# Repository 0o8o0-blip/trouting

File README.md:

# Trouting: an autorouter for KiCad

Trouting (short for *Tommy's routing*) routes the tracks of a KiCad PCB for you. Give it a placed board with
a GND pour; it routes every net, stitches GND into the pour with vias, writes
the tracks back into the `.kicad_pcb` and runs KiCad's own DRC on the result.

*The demo board in `examples/demo/`, routed by Trouting in 24 seconds: 25
nets, every pad connected, no new DRC violations. Red is the front, blue is the GND
pour on the back with the back-side tracks cut into it.*

It is made for the boards most of us actually make: dense **2-layer boards with
a ground pour**, QFNs, an ESP32 module, fine-pitch connectors.

- **All nets at once.** It doesn't route one net after another and get stuck
  on the last few. Every net is routed every round, and spots that several
  nets want get more expensive each round (negotiated congestion, the
  PathFinder algorithm from FPGA routing). The net that has another way moves;
  the one that needs the spot keeps it.
- **Understands pours.** GND isn't routed pad to pad: each pad gets a short
  track and a via into the pour. Trouting predicts how KiCad will fill the
  zones, so it knows which bits of pour will be cut off, and stitches those
  too. Thermal reliefs are checked the way KiCad's DRC checks them.
- **Your board's rules.** Clearances, track widths and via sizes come from
  the board's net classes (`.kicad_pro`) and custom rules (`.kicad_dru`).
  Power nets keep their width where it fits and narrow only where it doesn't,
  and you are told where.
- **Checked by KiCad.** After routing, KiCad's DRC runs on the result and
  Trouting reports any violation that wasn't there before.
- **Native to KiCad.** No Java and no Specctra DSN/SES export and import. It
  reads and writes the `.kicad_pcb` through KiCad's own Python module.

Status: young but working. On the public [PCBWorld](https://github.com/LGAI-Research/PCBWorld)
benchmark it routes all 119 boards fully connected and free of DRC errors (see Results). It runs
on Linux, Windows and macOS with KiCad 9 and 10.

## In KiCad: the plugin

Trouting can run from KiCad's PCB editor: a toolbar button routes the open
board, and Ctrl+Z takes the routes out again. When the board can't be routed
as placed, the result window lists the suggested moves, and "Make this move
and route again" does just that.

To install it, download the `trouting-…-pcm.zip` from the
[latest release](https://github.com/TommyHolt/trouting/releases/latest). In
KiCad, open **Plugin and Content Manager > Install from File**, pick the zip,
then restart the PCB editor. The same zip works on Linux, Windows and macOS.

From a checkout, `python3 tools/make_pcm.py` builds the zip into `dist/`, and
on Linux `tools/install_plugin.sh` links the plugin into KiCad instead, for
development.

The first time you click it, it asks to install numpy, scipy and shapely into
its own folder: a 55 MB download, with KiCad's pip (KiCad's AppImage has none:
then the plugin fetches the same packages from PyPI itself, each checked
against PyPI's SHA-256). The router runs in a
process of its own, so the editor stays responsive and you can cancel.

It works with KiCad 9 and 10 on Linux, 64-bit Windows and macOS (Apple
Silicon and Intel). On Linux it is tested with the KiCad 9 snap and KiCad's
AppImage. On Windows, on an Apple Silicon Mac and with the AppImage on Linux,
every change is tested on GitHub Actions with KiCad 9 and 10 from their
installers: the package install and the whole routing run, up to a clean DRC.
The Intel Mac build is made but not tested.

It routes 12 setups at once and keeps the best, so it is quicker the more cores
you have: the stuck demo below, suggestions included, takes about 7 minutes on
12 cores and over 20 on 4. It runs no more setups at once than fit in the free
memory (each needs a few hundred MB on a typical board), so it won't push the
machine into swap. It takes as long as it needs; `--max-minutes M`
stops it after M minutes, when each setup keeps its best try and the nets it
couldn't route are listed.

## From the command line

You need:

- **KiCad 9 or 10.** On Linux, tested with the snap (`sudo snap install kicad`); a
  normal install should also work if your system Python can `import pcbnew`.
  On Windows, the normal installer: Trouting finds KiCad in Program Files (or
  set `KICAD_PYTHON` to the `python.exe` in KiCad's `bin` folder). On macOS,
  KiCad in Applications: Trouting finds the Python inside `KiCad.app` (or set
  `KICAD_PYTHON`).
- **Python 3.9 or newer** with numpy, scipy, shapely and Pillow.
- **A C compiler**, for the search core, a small C file compiled the first time
  it runs. On Linux, gcc. On macOS, clang (`xcode-select --install`). On
  Windows, either gcc from MinGW-w64, or no compiler: copy
  `plugins/trouting/prebuilt/core-…-win32-amd64.dll` out of the release zip
  into `trouting/prebuilt/`.

```sh
git clone https://github.com/TommyHolt/trouting.git
cd trouting
pip install -r requirements.txt
```

Then:

```sh
./trouting.py board.kicad_pcb                      # route in place, keeps board.kicad_pcb.trouting-bak
./trouting.py board.kicad_pcb -o routed.kicad_pcb  # write somewhere else
./trouting.py board.kicad_pcb --keep-tracks        # keep the tracks already there, route the rest
./trouting.py board.kicad_pcb --png routed.png     # also draw the result: front red, back blue, vias white
./trouting.py board.kicad_pcb --plane-cost 1000    # keep signal tracks off the plane layers where it can
```

On Windows, run it as `python trouting.py …`. On macOS, `python3 trouting.py …`
keeps the Mac awake while it routes (it uses `caffeinate`).

To try it on the demo board (a made-up USB-C microcontroller board, placed
but not routed):

```sh
./trouting.py examples/demo/demo.kicad_pcb -o demo-routed.kicad_pcb
./trouting.py examples/demo/stuck.kicad_pcb -o stuck-routed.kicad_pcb   # placed too tight: shows the suggestions
```

Close the board in KiCad first, or reload it after. Keep the `.kicad_pro` (and
`.kicad_dru`, if you have one) next to the `.kicad_pcb`: that is where the net
classes and rules are. Tracks you have **locked** in KiCad are kept.

It runs twelve router setups in parallel (one per core) and keeps the best: the
fewest unrouted connections, then the fewest vias, then the shortest copper.
A run looks like this:

```
reading board.kicad_pcb
  dumped 2 copper layers, 50 footprints, 70 pads, 13 nets, 0 tracks, 0 vias
board read: 1003 x 503 cells x 2 layers, 13 nets to join (0.8s)
  setup via  8.0, plane 1.0:  0 unrouted,   0 vias,    184 mm  (1 rounds, 0s)
  setup via  8.0, plane 1.5:  0 unrouted,  14 vias,    186 mm  (4 rounds, 1s)
  ...
best: via cost 8.0, plane cost 1.0
  applied 66 tracks, 0 vias
wrote board.kicad_pcb  (5s)

all connections routed
KiCad DRC: 0 unconnected pads (was 0)
  no new violations
```

### When a board can't be routed as placed

Then Trouting looks for a part to move or rotate. It takes the parts near the
connections it couldn't make and tries turning them and shifting them by 0.5
to 2 mm. A move must keep the part's courtyard clear of the other parts, its
pads clear of other copper, and the part as far inside the board as it was.
Trouting ranks the moves by how much shorter and less tangled the ratsnest
gets, then routes the whole board with each of the best ones. Only moves that
leave fewer connections unrouted are listed. On `examples/demo/stuck.kicad_pcb`
(the demo with U1 turned and C5 moved up):

```
not routed (3):
  ADC1                     U1.10
  SDA                      U1.13
  TX                       U1.11
  crowded at: (123.50, 112.30)
to make it route, move or rotate a part (each checked by routing the board with it):
  move C5 0.5 mm right and down (to 124.15, 114.15)  routes fully
  move C5 2.0 mm down (to 123.80, 115.80)            routes fully
  rotate U1 90° clockwise (to 0°)                    2 left unrouted
  move U1 1.0 mm down (to 120.00, 114.00)            2 left unrouted
```

This takes about as long again as the routing. `--no-suggest` skips it.

## Results

**PCBWorld** ([arXiv:2607.05915](https://arxiv.org/abs/2607.05915)), a public routing benchmark
on real open-source KiCad boards, scored by its own pipeline with KiCad's DRC. Clean pass: the
share of boards fully connected *and* with zero DRC errors.

| Set | Boards | Trouting | KiCadRoutingTools 0.24.1 | Freerouting | Best RL agent |
|---|---|---|---|---|---|
| D3-A | 99 | **1.00** | 0.92 | 0.80 | 0.94 |
| D3-B | 10 | **1.00** | 0.50 | 0.78 | 0.45 |
| D3-C | 10 | **1.00** | 0.50 | – | – |

KiCadRoutingTools is its current version (November 2026), run here with PCBWorld's own setup for
it; Freerouting's and the RL agent's numbers are the paper's. Both Trouting and KiCadRoutingTools
connect every board; the difference is DRC errors, and Trouting uses fewer vias (12.6 against 17.9
per D3-B board, 56 against 85 per D3-C board). The D3 boards are small to medium (D3-A: 6 to 31
pads); how it was run, the cross-checks and the caveats are in [docs/benchmarks.md](docs/benchmarks.md).

**37 boards with 4 or more layers** from the collection PCBWorld's boards come from (36 with 4
layers, one with 8 layers and 1585 pads), scored the same way. Clean pass:

| Trouting | KiCadRoutingTools 0.24.1 | The original hand routing |
|---|---|---|
| **34 of 37** | 8 of 37 | 36 of 37 |

Trouting's three misses are pins it can't get out from under dense chips.

**31 public, hand-routed boards** from GitHub (53 to 667 pads, six of them 4-layer): 28 end with
every pad connected. **Ten boards of our own** (2-layer, 3 to 64 nets): all ten.

## Limitations

What it doesn't do yet:

- **Escaping fine-pitch chips** (QFP, BGA) on dense boards: where many pins have to get out
  from under one chip, it can leave a few of them unrouted.
- **Big, dense boards can take hours.** A 4-layer board with 1151 pads and two fine-pitch chips
  still had 11 connections unrouted after 3 hours.
- **Pours on nets other than the plane net** (a +3V3 pour, say) aren't
  modelled, so they can be left with isolated copper.
- **Differential pairs and length matching** are not supported.
- **Placement suggestions move one part at a time.** A board that needs two
  parts moved gets the move that helps most, and you run it again.

Bug reports with a board attached are the most useful thing you can send.

## How it works

| file | what it does |
|---|---|
| `trouting_kicad.py` | The only part that needs KiCad's Python (pcbnew). `dump` reads a board into JSON; `apply` writes the tracks and vias back and refills the zones. |
| `trouting/board.py` | The board as a grid at 0.05 mm: exact distance to fixed copper, board edge, keepouts and holes; the pads each net must join. |
| `trouting/core.c` | A* search and the occupancy bookkeeping, in C. |
| `trouting/router.py` | The negotiated-congestion rounds, GND stitching, the pour model, thermal checks, and rip-up and repair. |
| `trouting/cli.py` | The command: runs the setups in parallel, applies the best, runs DRC before and after. |
| `trouting/suggest.py` | Placement suggestions: moves near the trouble, screened by the ratsnest, checked by routing. |
| `trouting/parallel.py` | The worker processes: fork and pipes on Linux (KiCad's snap doesn't allow the semaphores `multiprocessing` needs), a spawn pool on Windows and macOS. |
| `trouting/job.py`, `plugin/` | The KiCad plugin: the dialogs, and the router run as a job of its own. |

## Developing

Test boards are not part of the repository, because they are other people's
designs. Put your own in `test/boards/`: the `.kicad_pcb` with its
`.kicad_pro` and `.kicad_dru` next to it. The folder is git-ignored. Judge
every change on all of them, not on one.

```sh
test/bench.sh                     # route them all; table in test/out/bench/summary.txt
test/bench.sh mine other          # just these (test/boards/mine.kicad_pcb, ...)
test/run.sh mine via_cost=8.0     # one setup, in-process (PNG of the result), then KiCad's DRC
python3 test/t_suggest.py mine scan          # turn each part, list the turns that stop it routing
python3 test/t_suggest.py mine fix U2:270    # break it so, then see what the suggestions find
```

## License

MIT. See [LICENSE](LICENSE).

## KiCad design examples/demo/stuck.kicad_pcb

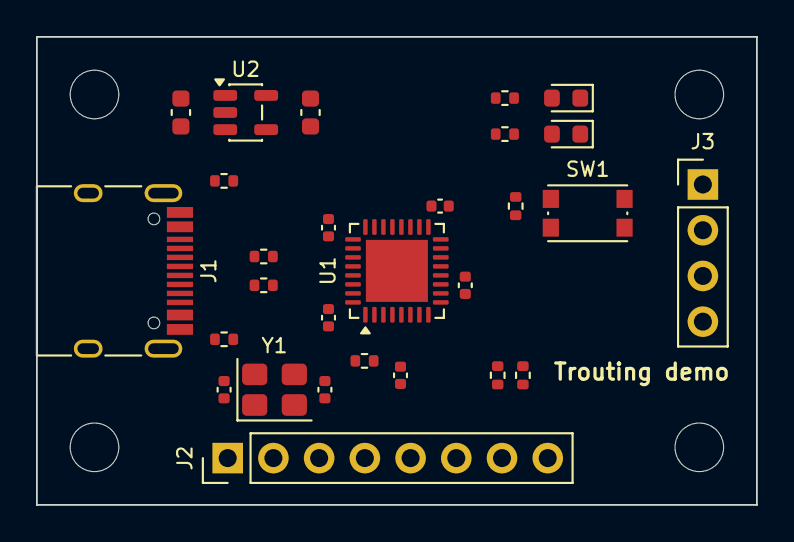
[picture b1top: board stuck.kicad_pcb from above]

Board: 2 copper layers, 40.0 x 26.0 mm, 32 parts (0 on the bottom side), 25 nets, no tracks yet.

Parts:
C1, C2: 1u; C_0603_1608Metric
C3, C4, C5, C6, C9: 100n; C_0402_1005Metric
C7, C8: 12p; C_0402_1005Metric
D1: green; LED_0603_1608Metric
D2: red; LED_0603_1608Metric
H1, H2, H3, H4: M2.5; MountingHole_2.7mm_M2.5
J1: USB-C; USB_C_Receptacle_HRO_TYPE-C-31-M-12
J2: I/O; PinHeader_1x08_P2.54mm_Vertical
J3: SWD; PinHeader_1x04_P2.54mm_Vertical
R1, R2: 5k1; R_0402_1005Metric
R3, R4: 1k; R_0402_1005Metric
R5, R10: 10k; R_0402_1005Metric
R6, R7: 4k7; R_0402_1005Metric
R8, R9: 22; R_0402_1005Metric
SW1: BOOT; SW_Push_1P1T_NO_CK_KMR2
U1: MCU; QFN-32-1EP_5x5mm_P0.5mm_EP3.45x3.45mm
U2: LDO 3.3V; SOT-23-5
Y1: 16MHz; Crystal_SMD_3225-4Pin_3.2x2.5mm

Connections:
+3V3: C2.1, C3.1, C4.1, C5.1, C6.1, J2.1, J3.1, R5.1, R6.1, R7.1, R10.1, U1.1, U1.8, U1.17, U1.25, U2.5
ADC0: J2.7, U1.9
ADC1: J2.8, U1.10
BTN: R5.2, SW1.1, U1.28
CC1: J1.A5, R1.1
CC2: J1.B5, R2.1
GND: C1.2, C2.2, C3.2, C4.2, C5.2, C6.2, C7.2, C8.2, C9.2, D1.1, D2.1, J1.A1, J1.A12, J1.B1, J1.B12, J1.S1, J2.2, J3.4, R1.2, R2.2, SW1.2, U1.4, U1.16, U1.24, U1.33, U2.2, Y1.2, Y1.4
LED1: R3.1, U1.26
LED1_A: D1.2, R3.2
LED2: R4.1, U1.27
LED2_A: D2.2, R4.2
NRST: C9.1, R10.2, U1.7
RX: J2.6, U1.12
SCL: J2.4, R7.2, U1.14
SDA: J2.3, R6.2, U1.13
SWCLK: J3.3, U1.19
SWDIO: J3.2, U1.18
TX: J2.5, U1.11
USB_DM: R8.2, U1.2
USB_DM_C: J1.A7, J1.B7, R8.1
USB_DP: R9.2, U1.3
USB_DP_C: J1.A6, J1.B6, R9.1
VBUS: C1.1, J1.A4, J1.A9, J1.B4, J1.B9, U2.1, U2.3
XIN: C7.1, U1.5, Y1.1
XOUT: C8.1, U1.6, Y1.3
